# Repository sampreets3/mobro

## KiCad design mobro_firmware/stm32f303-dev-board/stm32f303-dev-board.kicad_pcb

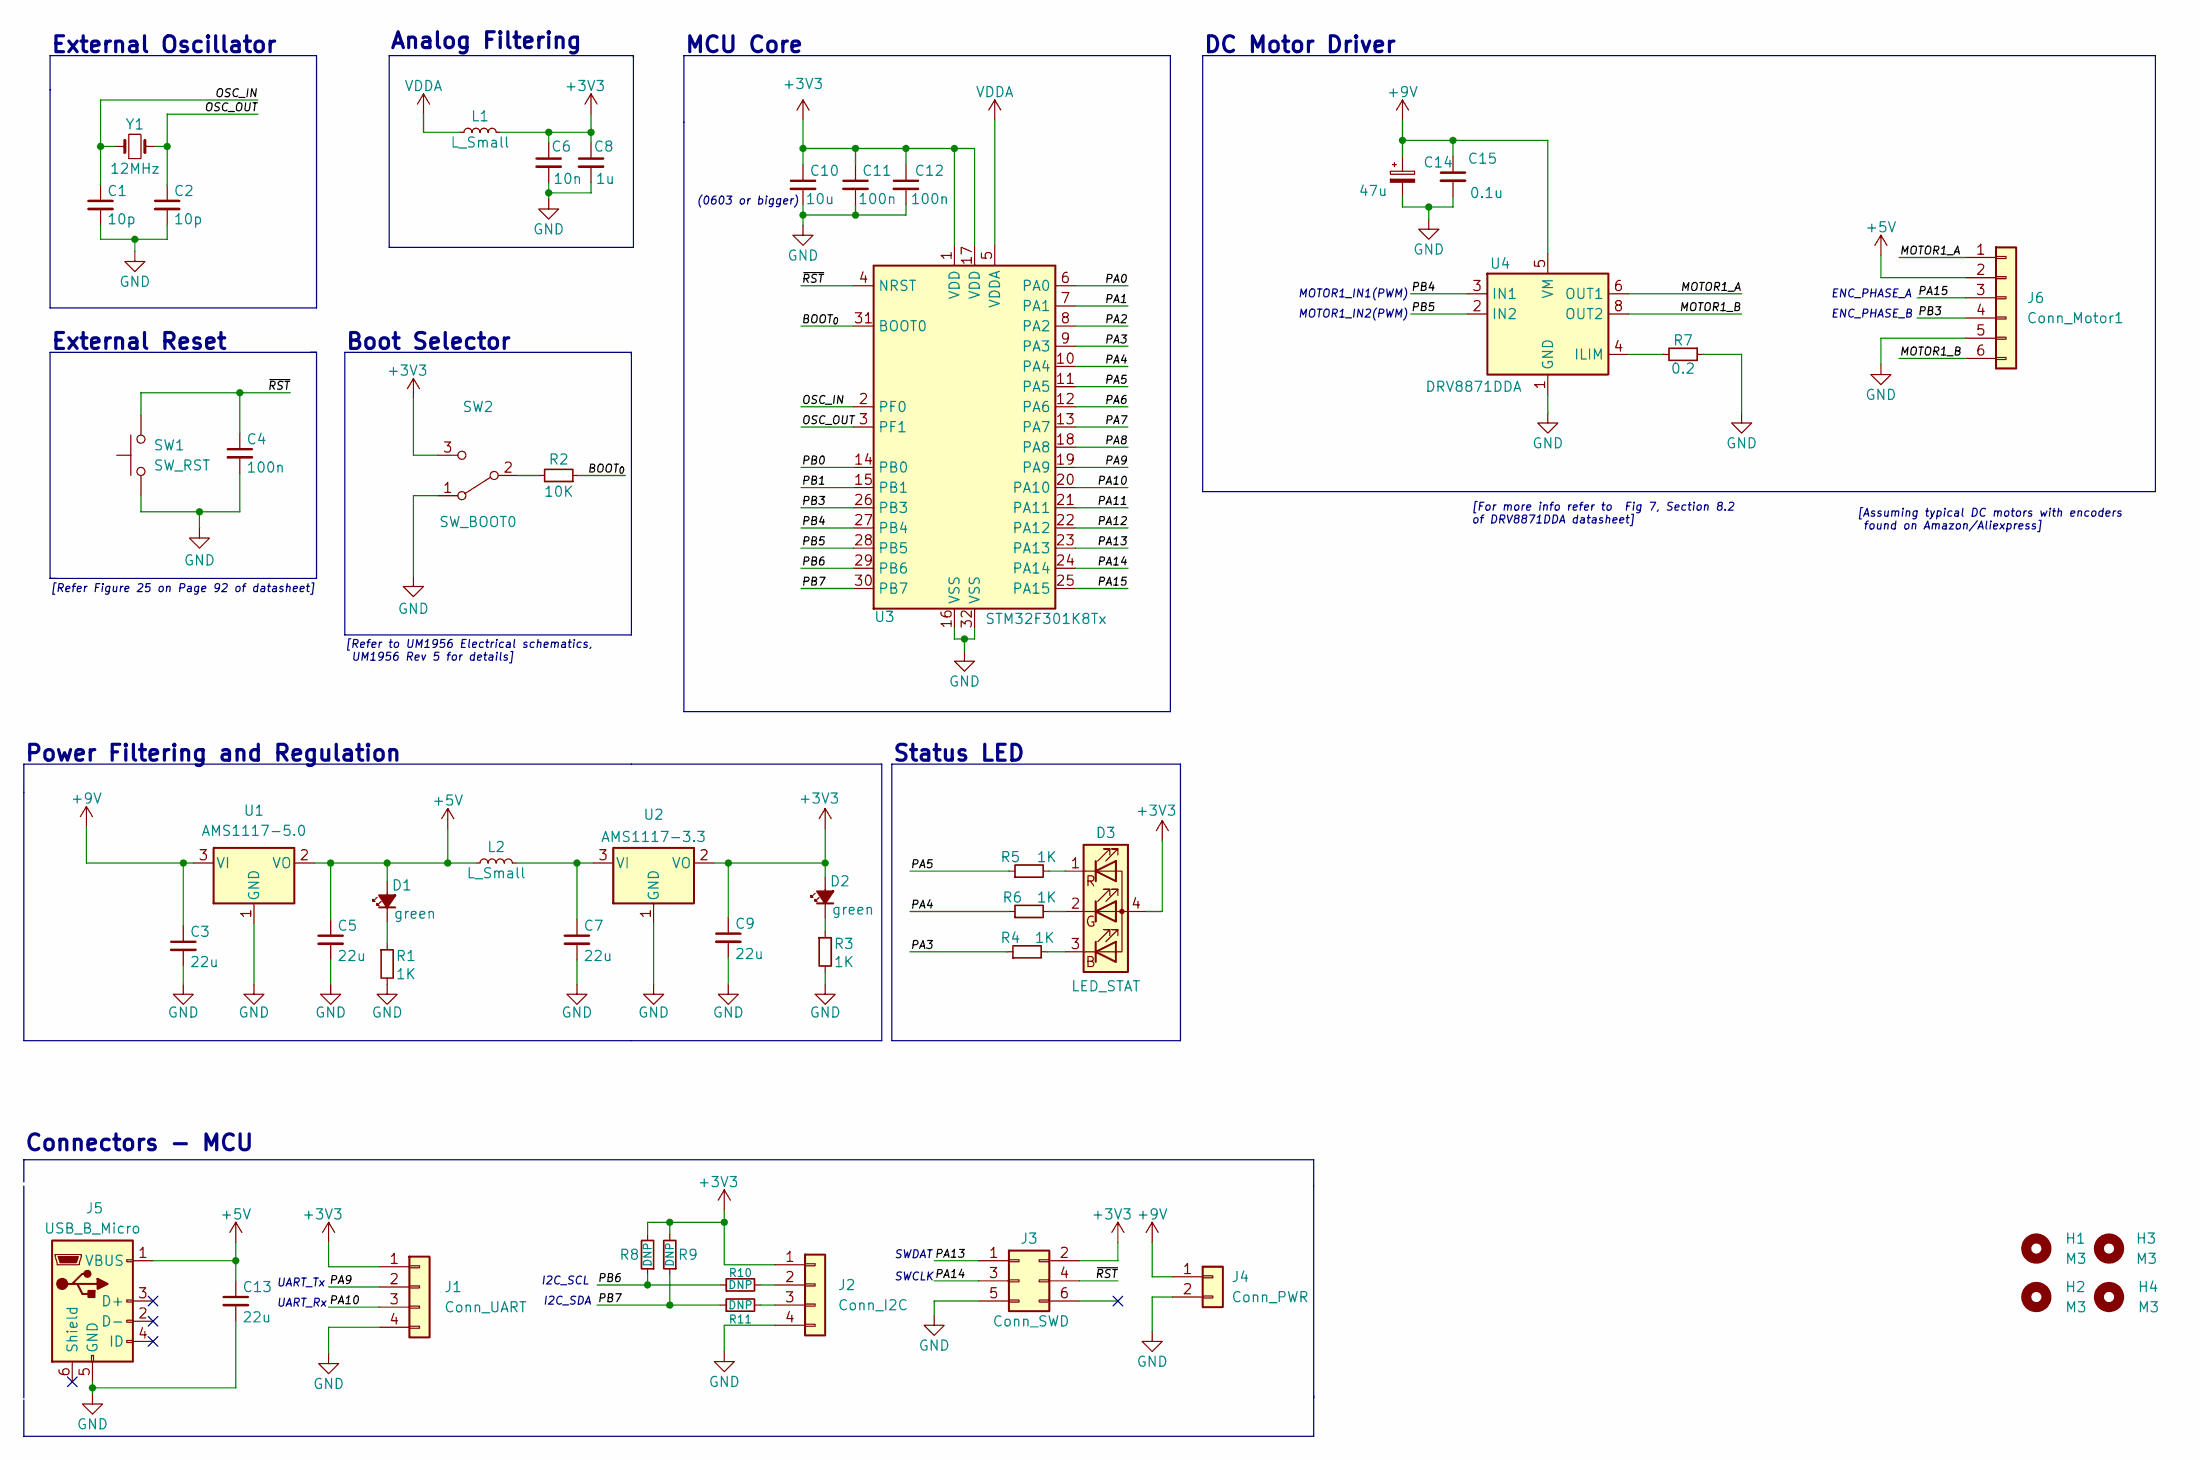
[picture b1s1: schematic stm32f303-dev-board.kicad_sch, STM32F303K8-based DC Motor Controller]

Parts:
C1, C2: 10p; C_0402_1005Metric
C3, C5, C7, C9, C13: 22u; C_0603_1608Metric
C4, C11, C12: 100n; C_0402_1005Metric
C6: 10n; C_0402_1005Metric
C8: 1u; C_0402_1005Metric
C10: 10u; C_0603_1608Metric
C14: 47u; CP_Elec_4x3.9
C15: 0.1u; C_0402_1005Metric
D1, D2: green; LED_0603_1608Metric
D3: LED_STAT; LED_RGB_1210
H1, H2, H3, H4: M3; MountingHole_2.7mm_M2.5
J1: Conn_UART; JST_PH_S4B-PH-K_1x04_P2.00mm_Horizontal
J2: Conn_I2C; JST_PH_S4B-PH-K_1x04_P2.00mm_Horizontal
J3: Conn_SWD; PinSocket_2x03_P2.54mm_Vertical
J4: Conn_PWR; JST_PH_S2B-PH-K_1x02_P2.00mm_Horizontal
J5: USB_B_Micro; USB_Micro-B_Molex-105017-0001
J6: Conn_Motor1; JST_PH_S6B-PH-K_1x06_P2.00mm_Horizontal
L1, L2: L_Small; L_0603_1608Metric
R1, R3, R4, R5, R6: 1K; R_0402_1005Metric
R2: 10K; R_0402_1005Metric
R7: 0.2; R_0402_1005Metric
R8, R9, R10, R11: DNP; R_0402_1005Metric
SW1: SW_RST; SW_PUSH_6mm_H4.3mm
SW2: SW_BOOT0; SW_SPDT_PCM12
U1: AMS1117-5.0; SOT-223-3_TabPin2
U2: AMS1117-3.3; SOT-223-3_TabPin2
U3: STM32F301K8Tx; LQFP-32_7x7mm_P0.8mm
U4: DRV8871DDA; Texas_HTSOP-8-1EP_3.9x4.9mm_P1.27mm_EP2.95x4.9mm_Mask2.4x3.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
Y1: 12MHz; Crystal_SMD_0603-2Pin_6.0x3.5mm

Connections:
+3V3: C6.1, C8.1, C9.1, C10.1, C11.1, C12.1, D2.2 (A), D3.4 (A), J1.1, J2.1, J3.2, L1.2, R8.2, R9.2, SW2.3 (C), U2.2 (VO), U3.1 (VDD), U3.17 (VDD)
+5V: C5.1, C13.1, D1.2 (A), J5.1 (VBUS), J6.2, L2.1, U1.2 (VO)
+9V: C3.1, C14.1, C15.1, J4.1, U1.3 (VI), U4.5 (VM)
/BOOT_{0}: R2.1, U3.31 (BOOT0)
/MOTOR1_A: J6.1, U4.6 (OUT1)
/MOTOR1_B: J6.6, U4.8 (OUT2)
/OSC_IN: C1.1, U3.2 (PF0), Y1.1
/OSC_OUT: C2.1, U3.3 (PF1), Y1.2
/PA0: U3.6 (PA0)
/PA1: U3.7 (PA1)
/PA2: U3.8 (PA2)
/PA3: R4.1, U3.9 (PA3)
/PA4: R6.1, U3.10 (PA4)
/PA5: R5.1, U3.11 (PA5)
/PA6: U3.12 (PA6)
/PA7: U3.13 (PA7)
/PA8: U3.18 (PA8)
/PA9: J1.2, U3.19 (PA9)
/PA10: J1.3, U3.20 (PA10)
/PA11: U3.21 (PA11)
/PA12: U3.22 (PA12)
/PA13: J3.1, U3.23 (PA13)
/PA14: J3.3, U3.24 (PA14)
/PA15: J6.3, U3.25 (PA15)
/PB0: U3.14 (PB0)
/PB1: U3.15 (PB1)
/PB3: J6.4, U3.26 (PB3)
/PB4: U3.27 (PB4), U4.3 (IN1)
/PB5: U3.28 (PB5), U4.2 (IN2)
/PB6: R8.1, R10.1, U3.29 (PB6)
/PB7: R9.1, R11.1, U3.30 (PB7)
/~RST: C4.1, J3.4, SW1.2, U3.4 (NRST)
GND: C1.2, C2.2, C3.2, C4.2, C5.2, C6.2, C7.2, C8.2, C9.2, C10.2, C11.2, C12.2, C13.2, C14.2, C15.2, J1.4, J2.4, J3.5, J4.2, J5.5 (GND), J6.5, R1.2, R3.2, R7.1, SW1.1, SW2.1 (A), U1.1 (GND), U2.1 (GND), U3.16 (VSS), U3.32 (VSS), U4.1 (GND), U4.7 (GND), U4.9 (GND)
unnamed: C7.1, L2.2, U2.3 (VI)
unnamed: D1.1 (K), R1.1
unnamed: D2.1 (K), R3.1
unnamed: D3.1 (RK), R5.2
unnamed: D3.2 (GK), R6.2
unnamed: D3.3 (BK), R4.2
unnamed: J2.2, R10.2
unnamed: J2.3, R11.2
unnamed: R2.2, SW2.2 (B)
unnamed: R7.2, U4.4 (ILIM)
VDDA: L1.1, U3.5 (VDDA)

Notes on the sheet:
[Assuming typical DC motors with encoders found on Amazon/Aliexpress]
ENC_PHASE_A
DC Motor Driver
External Oscillator
SWDAT
I2C_SDA
Analog Filtering
[Refer to UM1956 Electrical schematics, UM1956 Rev 5 for details]
MOTOR1_IN1(PWM)
[Refer Figure 25 on Page 92 of datasheet]
External Reset
Connectors - MCU
I2C_SCL
(0603 or bigger)
ENC_PHASE_B
MOTOR1_IN2(PWM)
Power Filtering and Regulation
UART_Rx
MCU Core
Boot Selector
Status LED
[For more info refer to Fig 7, Section 8.2 of DRV8871DDA datasheet]
UART_Tx
SWCLK

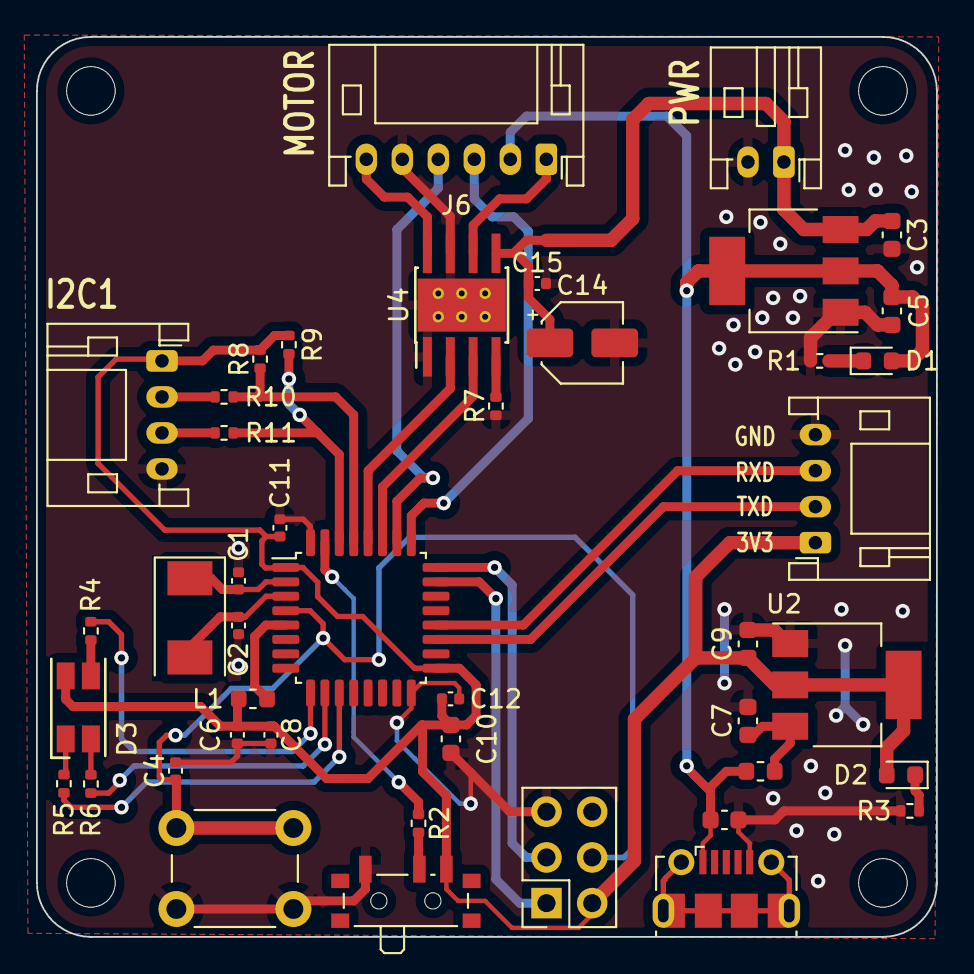
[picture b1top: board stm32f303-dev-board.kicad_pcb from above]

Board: 2 copper layers, 50.0 x 50.0 mm, 48 parts (0 on the bottom side), 34 nets.

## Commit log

2023-01-18 Added gitignore file
2023-01-18 Added initial schematics and pcb for motor control board
